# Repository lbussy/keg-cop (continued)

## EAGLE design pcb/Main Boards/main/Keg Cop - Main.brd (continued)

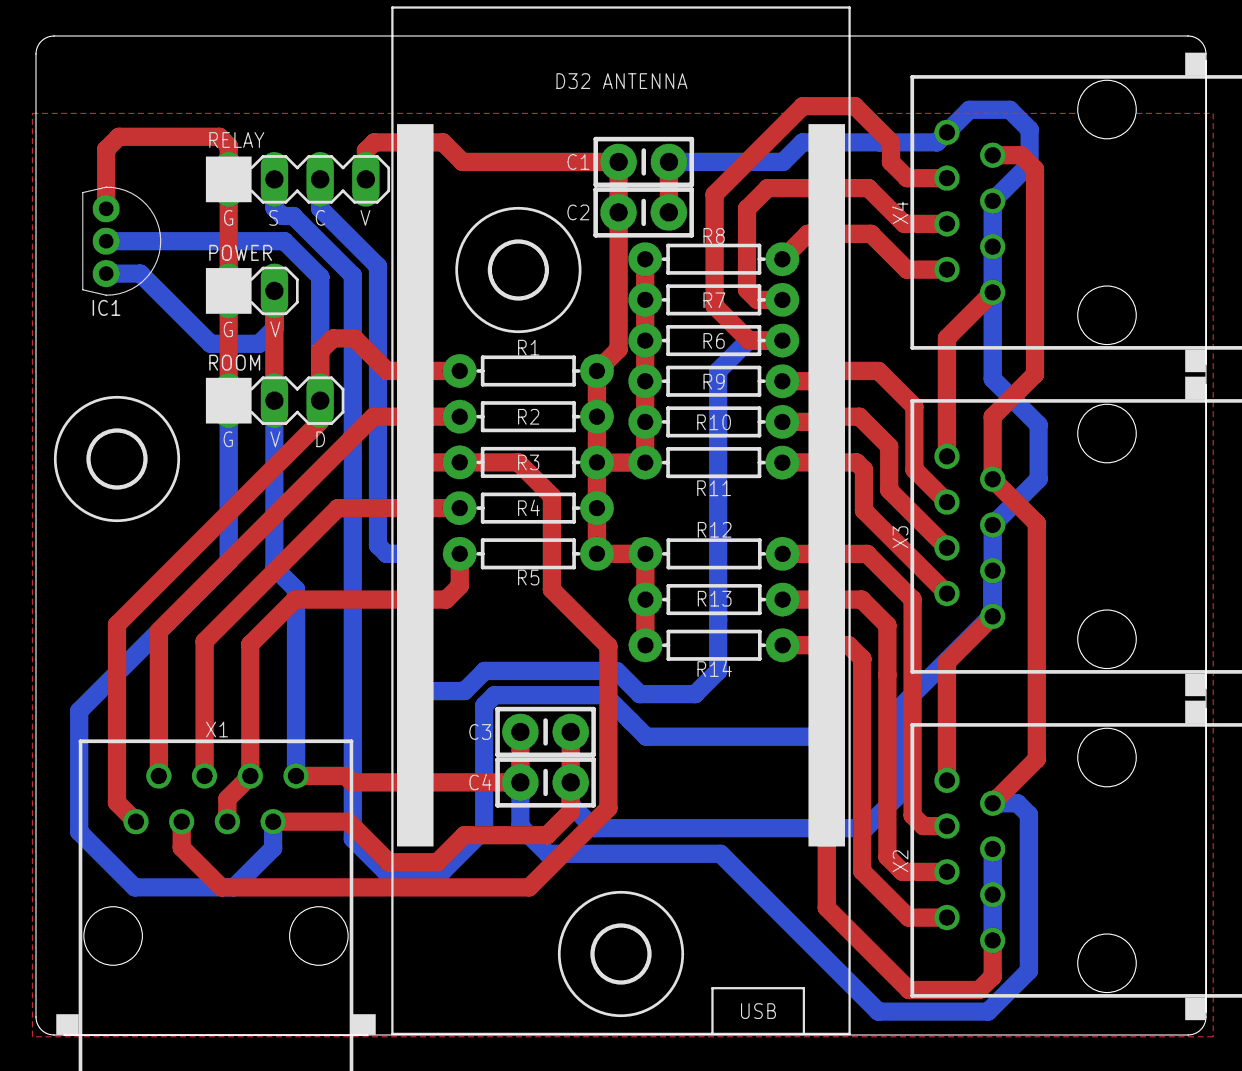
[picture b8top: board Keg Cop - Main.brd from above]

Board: 2 copper layers, 65.0 x 55.5 mm, 30 parts (0 on the bottom side), 19 nets.

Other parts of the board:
U$1, U$2, U$3: 3,0

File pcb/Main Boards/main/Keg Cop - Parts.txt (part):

Partlist exported from C:/Users/lee/OneDrive/Documents/GitHub/keg-cop/pcb/Main Boards/main/Keg Cop - Main.sch at 3/30/2021 6:56 PM

Part  Value     Device               Package        Description                                                                                 ARROW_PART_NUMBER ARROW_PRICE-STOCK DESCRIPTION                           HEIGHT MANUFACTURER_NAME MANUFACTURER_PART_NUMBER MF MOUSER_PART_NUMBER MOUSER_PRICE-STOCK                                                                                     MPN     OC_FARNELL OC_NEWARK POPULARITY PROD_ID VALUE
C1    0.1μF     CAP_CERAMIC_2.54     CAP_PTH-2.54                                                                                                                                                                                                                                                                                                                                                                                                             
C2    1.0μF     CAP_CERAMIC_2.54     CAP_PTH-2.54                                                                                                                                                                                                                                                                                                                                                                                                             
C3    0.1μF     CAP_CERAMIC_2.54     CAP_PTH-2.54                                                                                                                                                                                                                                                                                                                                                                                                             
C4    1.0μF     CAP_CERAMIC_2.54     CAP_PTH-2.54                                                                                                                                                                                                                                                                                                                                                                                                             
D32   Lolin D32 WEMOS-D32D32_NO_BATT D32_NO_BATT    D32_REVERSE is a Reverse silkscreen for placing the Wemos D32 on the underside of the board                                                                                                                                                                                                                                                                                                               
IC1   DS18B20+  DS18B20+             TO-92          DS18B20 prog thermometer 1-Wire, TO92                                                       DS18B20+                            DS18B20 prog thermometer 1-Wire, TO92 mm     Maxim Integrated  DS18B20+                    700-DS18B20+       https://www.mouser.co.uk/ProductDetail/Maxim-Integrated/DS18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                                                      
POWER 2-PIN     HDR-2                HDR-2_VERT                                                                                                                                                                                                                                                                                                                                                                                                               
R1    2.2kΩ     RESISTORAXIAL-0.3    AXIAL-0.3      Generic Resistor Package                                                                                                                                                                                                                                                                                                                                                                                  
R2    2.2kΩ     RESISTORAXIAL-0.3    AXIAL-0.3      Generic Resistor Package                                                                                                                                                                                                                                                                                                                                                                                  
R3    2.2kΩ     RESISTORAXIAL-0.3    AXIAL-0.3      Generic Resistor Package                                                                                                                                                                                                                                                                                                                                                                                  
R4    2.2kΩ     RESISTORAXIAL-0.3    AXIAL-0.3      Generic Resistor Package                                                                                                                                                                                                                                                                                                                                                                                  
R5    2.2kΩ     RESISTORAXIAL-0.3    AXIAL-0.3      Generic Resistor Package                                                                                                                                                                                                                                                                                                                                                                                  
R6    2.2kΩ     RESISTORAXIAL-0.3    AXIAL-0.3      Generic Resistor Package                                                                                                                                                                                                                                                                                                                                                                                  
R7    2.2kΩ     RESISTORAXIAL-0.3    AXIAL-0.3      Generic Resistor Package                                                                                                                                                                                                                                                                                                                                                                                  
R8    2.2kΩ     RESISTORAXIAL-0.3    AXIAL-0.3      Generic Resistor Package                                                                                                                                                                                                                                                                                                                                                                                  
R9    2.2kΩ     RESISTORAXIAL-0.3    AXIAL-0.3      Generic Resistor Package                                                                                                                                                                                                                                                                                                                                                                                  
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
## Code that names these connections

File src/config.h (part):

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// Input pin for keg 0 flow
//
#ifndef FLOW0
#define FLOW0 4
#endif
//
//////////////////////////////////////////////////////////////////////////
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// Input pin for keg 1 flow
//
#ifndef FLOW1
#define FLOW1 16
#endif
//
//////////////////////////////////////////////////////////////////////////
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// Input pin for keg 2 flow
//
#ifndef FLOW2
#define FLOW2 17
#endif
//
//////////////////////////////////////////////////////////////////////////
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// Input pin for keg 3 flow
//
#ifndef FLOW3
#define FLOW3 18
#endif
//
//////////////////////////////////////////////////////////////////////////
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// Input pin for keg 4 flow
//
#ifndef FLOW4
#define FLOW4 19
#endif
//
//////////////////////////////////////////////////////////////////////////
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// Input pin for keg 5 flow
//
#ifndef FLOW5
#define FLOW5 21
#endif
//
//////////////////////////////////////////////////////////////////////////
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// Input pin for keg 6 flow
//
#ifndef FLOW6
#define FLOW6 22
#endif
//
//////////////////////////////////////////////////////////////////////////
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// Input pin for keg 7 flow
//
#ifndef FLOW7
#define FLOW7 23
#endif
//
//////////////////////////////////////////////////////////////////////////
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// Input pin for keg 8 flow
//
#ifndef FLOW8
#define FLOW8 13
#endif
//
//////////////////////////////////////////////////////////////////////////
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
//////////////////////////////////////////////////////////////////////////
//
// Define cool actuator pin
//
#ifndef COOL
#define COOL 27
#endif
//
//////////////////////////////////////////////////////////////////////////
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
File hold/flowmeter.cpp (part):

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const char *kegfilename = "/kegs.json";
extern const size_t capacityKegDeserial = JSON_ARRAY_SIZE(8) + JSON_OBJECT_SIZE(1) + 8*JSON_OBJECT_SIZE(8) + 770;
extern const size_t capacityKegSerial = JSON_ARRAY_SIZE(8) + JSON_OBJECT_SIZE(1) + 8*JSON_OBJECT_SIZE(8);
int kegPins[8] = {KEG0, KEG1, KEG2, KEG3, KEG4, KEG5, KEG6, KEG7};
Flowmeter flow;

static IRAM_ATTR void HandleIntISR0(void)
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
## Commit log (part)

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2022-09-05 Move JSON to stack
2022-09-05 Cleanup strings
2022-09-06 Move back to dynamic type
2022-09-07 Move common function to common file
2022-09-07 Allow builds outside of a repo
2022-09-07 Refactor API
2022-09-08 Add semaphores to prevent windup
2022-09-09 Use SPIFFS Editor
2022-09-09 Finish vestigial file management
2022-09-09 Fix API docs
2022-09-09 Fix API docs (#132)
2022-09-09 Move secret to a header (#133)
2022-09-09 Fix alert bars
2022-09-09 Fix alert bars (#134)
2022-09-09 Enable menu change on sensor change (#135)
2022-09-09 Version bump
2022-09-12 Update KSTV keys
2022-09-12 Remove debug condition on Telnet
2022-09-12 Cleanup debug (#136)
    * Add kstv.json
    * Update KSTV keys
    * Remove debug condition on Telnet
    * Remove debug condition on /edit
2022-09-12 Make keys public, add functions for KS-TV
2022-09-12 Remove needless keys, move KS-TV
2022-09-12 Fix a couple mistakes
2022-09-12 Kstv json (#137)
    * Add kstv.json
    * Update KSTV keys
    * Cleanup debug (#136)
    * Add kstv.json
    * Update KSTV keys
    * Remove debug condition on Telnet
2022-09-12 Don't need string
2022-09-12 Don't need string (#138)
2022-09-18 Move semaphore earlier
2022-09-18 Move reconnect out of callback
2022-09-18 Filesystem stability (#139)
    * Don't need string
    * Change to 5.0 class for SR-only
    * Move semaphore earlier
    * Move reconnect out of callback
    * Clean up filesystem logic
2022-09-18 Filesystem stability (#140)
    * Don't need string
    * Change to 5.0 class for SR-only
    * Move semaphore earlier
    * Move reconnect out of callback
    * Clean up filesystem logic
2022-09-18 Hide page when theme changes (#141)
2022-09-18 Update TODO
2022-09-21 Version update (#142)
2022-09-23 Remove kegscreen service advertisement
2022-09-25 Fix for #146
2023-04-07 Use proper div
2023-04-09 Go back to platform package 1.0.6
2023-04-11 Stub this in for later
2023-04-11 Explicit python decl
2023-04-11 Add .gz handler
2023-04-11 Update uptime refresh
2023-04-12 Ignore data
2023-04-12 I guess I don't need this
2023-04-12 Fix active links
2023-04-12 Fix fan control enabled assignment
2023-04-12 Fix for #152
2023-04-12 Fix for #149
2023-04-13 Version increment
2023-04-14 Restructure reconnect
2023-04-14 Restart serial and telnet
2023-04-14 Restart Web Server
2023-04-14 Reset main loop and filesystem
2023-04-14 Cleanup
2023-04-15 Cleanup logging
2023-04-15 Add some delays to allow Serial to start
2023-04-15 Lockout
2023-04-15 Separate stop and start
2023-04-15 Fix prefixes
2023-04-15 Loop logic
2023-04-15 Set autoconnect off
2023-04-15 Update Bootswatch
2023-04-15 Stub in hourly reboots
2023-04-15 Dis/reconnect on iter
2023-04-16 Reboot every 1 hour to avoid panic
2023-04-16 Logging cleanup
2023-04-16 Change to 2 hour reboot
2023-04-16 Standardize logic
2023-04-16 Tag new alpha
2023-04-18 Close FS after use
2023-04-19 Use single open/close
2023-04-19 Add delay to see startup Serial
2023-04-21 Fix John's 'feature'
2023-04-21 Refactor return
2023-04-22 Move theme to info
2023-04-23 Get rid of some harmless 404 erors
2023-04-23 Reset to 42 day reboot
2023-04-23 Add new file handler
2023-04-23 Fixed asynch error
2023-04-23 Update LCBUrl to HEAD
2023-04-23 Reverse order of debug
2023-04-23 Remove debug
2023-04-23 Change execution order
2023-04-25 Rearranged to allow flow load
2023-04-25 Nail down LCBUrl version
2023-04-29 Replace appconfig keys
2023-04-29 Add realm to authentication
2023-04-29 Stylize file buttons
2023-04-30 Add link to /fs/
2023-04-30 Style other buttons
2023-04-30 Exclude delete/download buttons
2023-04-30 Style/cancel upload
2023-05-11 Additional FS cleanup - stopping point
2023-05-11 Keep track of TODO
2023-05-11 Add debug
2023-05-11 Fix concatenation
2023-05-11 Add default TIO labels
2023-05-11 Fix label default
2023-05-11 Limit debug printing when file is missing
2023-05-11 Replace missing file
2023-05-11 Update version tag
2023-05-11 Realm is busted
2023-05-11 Restyle file list
2023-05-11 Disable/enable buttons
2023-05-11 Timeout messages
2023-05-11 Disable uploads
2023-05-13 Test uploads
2023-05-13 Rearrange events
2023-05-13 Pretty code
2023-05-13 Remive unused function
2023-05-13 Add secret to fs actions
2023-05-13 Add filename to prompt
2023-05-14 Restore file upload (#182)
    * Test uploads
    * Remove comments
    * Rearrange events
    * Pretty code
    * Remive unused function
    * Create new file upload
2023-05-14 Document fs page
2023-05-14 Remove /files/ from info
2023-05-14 Self-document fs API
2023-05-15 Split functions
2023-05-15 Document split fs api
2023-05-15 Fix file status display
2023-05-15 Update image
2023-05-15 Add fs api documentation
2023-05-15 Document fs (#183)
    * Document fs page
    * Self-document fs API
    * Fix file status display
    * Update image
    * Add fs api documentation
2023-05-15 Queue saves
2023-05-16 No longer used
2023-05-16 Use updated ArduinoJson
2023-05-16 Remove stupid workaround
2023-05-16 Add a better 404 handler
2023-05-16 Move to LittleFS
2023-05-16 Move license to md
2023-05-19 Littlefs (#186)
    * Move to LittleFS
    * Move license to md
2023-05-19 Avoid non reentrant code (#187)
2023-05-20 Fix viewport (#188)
2023-05-20 Rearrange fatal error
2023-05-20 Reset log priorities
2023-05-21 Add failure detect to app load
2023-05-21 Add debug to models
2023-05-21 Add handler for debug settings
2023-05-21 Add loglevel to serial init
2023-05-23 Add copy file function
2023-05-23 Leave notes
2023-05-23 Get rid of unneeded TODOs
2023-05-23 Use arguments for JSON load/save functions
2023-05-26 Update comments
2023-05-26 Leave myself a note
2023-05-29 Fix return
2023-05-29 Attempt config reload
2023-05-29 Backup config (#190)
    * Add failure detect to app load
    * Add copy file function
    * Handle LittleFS or SPIFFS
    * Use arguments for JSON load/save functions
    * Create backup after good file save
    * Fix return
2023-05-29 Backup config (#190)
    * Add failure detect to app load
    * Add copy file function
    * Handle LittleFS or SPIFFS
    * Use arguments for JSON load/save functions
    * Create backup after good file save
    * Fix return
2023-05-31 Update telnet lib
2023-05-31 Add telnet to web handler
2023-05-31 Add loglevel to web handler
2023-06-01 Add telnet and loglevel info
2023-06-01 Fix some scaling
2023-06-01 Change URL Target to Generic Rest
2023-06-01 Change URL Target to Generic Rest (#191)
2023-06-06 Bump version to Beta
2023-06-06 Fix docs requirements
2023-06-07 Handle LittleFS
2023-06-07 Add defaults
2023-06-07 Add back in async settings
2023-06-07 Restore saving theme
2023-06-07 Wrap debug settings in form
2023-06-07 Fix settings debug (#193)
    * Handle LittleFS
    * Fix debug line
    * Add defaults
    * Add back in async defines
    * Fix debug load
    * Restore saving theme
2023-06-08 Use explicit paths
2023-06-08 Reorder page handlers
2023-06-08 Fix routes
2023-06-08 Fs errors (#194)
    * Use explicit paths
    * Compress PNG too
    * Reorder page handlers
    * Fix routes
2023-06-08 Revert "Fs errors (#194)"
    This reverts commit 4d5f7bd300830cc77d4469af5861f50ff3dcb13e.
2023-06-08 Fs errors (#196)
    * Use explicit paths
    * Compress PNG too
    * Reorder page handlers
    * Fix routes
    * Turn off core debug
2023-06-08 Revert route changes
2023-06-08 Stub out nerw files
2023-06-08 New functions
2023-06-08 Start moving towards sync MQTT
2023-06-09 Remove RPints from setup
2023-06-09 Remove unused code
2023-06-09 Set up to use generic push
2023-06-09 No longer needed
2023-06-09 Move defines out of indiv headers
2023-06-09 Move wifihandler defines out of headers
2023-06-09 Move version defines out of headers
2023-06-09 Move urltarget defines out of headers
2023-06-09 Move uptimelog defines out of headers
2023-06-09 Move tools defines out of headers
2023-06-09 Move thermostat defines out of headers
2023-06-09 Move tempsensor defines out of headers
2023-06-09 Move taplistio defines out of headers
2023-06-09 Move resetreasons defines out of headers
2023-06-09 Move ntphandler defines out of headers
2023-06-09 Move main defines out of headers
2023-06-09 Move kegscreen defines out of headers
2023-06-09 Move flowconfig defines out of headers
2023-06-09 Move execota defines out of headers
2023-06-09 Move appconfig defines out of headers
2023-06-09 Protect Includes & Defines (#197)
    * Move defines out of indiv headers
    * Move wifihandler includes out of headers
    * Move webpagehandler includes out of headers
    * Move version includes out of headers
    * Move urltarget includes out of headers
    * Move uptimelog includes out of headers
2023-06-10 New RPints push
2023-06-10 Get rid of old notes
2023-06-10 Address templating and push logic
2023-06-10 Fix RPints template
2023-06-10 Fix pulse reports
2023-06-10 RPints push finished
2023-06-10 Switch MQTT Libs (#198)
    * Go back to a normal MQTT lib
    * Remove RPints from setup
    * Set up to use generic push
    * Protect Includes & Defines (#197)
    * New RPints push
    * Address templating and push logic
2023-06-11 Clean up logging
2023-06-11 Add HA config to settings
2023-06-11 Add Mosquitto setup steps to troubleshooting
2023-06-11 Update documentation for HA context
2023-06-11 Handle HA config post
2023-06-11 Add HA files
2023-06-12 Rough out functions
2023-06-16 Change field to password
2023-06-16 Initial device discovery
2023-06-16 Normalize abbrev
2023-06-20 Working templates
2023-06-21 Change log level
2023-06-21 Re-use portions of template
2023-06-21 Fix status for binaries
2023-06-21 Send only when enabled
2023-06-23 Initial HASS push on startup
2023-06-24 Remove spam
2023-06-24 Add in state changes
2023-06-25 Change default logging
2023-06-25 Queue HASS functions
2023-06-25 Queuing and availability
2023-06-25 GEt rid of vestigal JSON code
2023-06-25 Update MQTT documentation
2023-06-25 Use initial and ongoing timer for HASS
2023-06-25 Get rid of compiler warning
2023-06-25 Reduce logging level
2023-06-26 Add single point re-broadcast
2023-06-26 Fix solenoid state
2023-06-26 Fixed logic
2023-06-26 MQTT update for only selected sensor
2023-06-26 MQTT update for unavailable too
2023-06-26 Make change on tap post
2023-06-26 Reset control state on sensor unavail
2023-06-30 Disable CP when sensor is disabled
2023-06-30 Home asst (#199)
    * Switch MQTT Libs (#198)
    * Set up to use generic push
    * Protect Includes & Defines (#197)
    * New RPints push
    * Address templating and push logic
    * Get rid of 24hr timer
2023-07-08 Add kickdetect to web settings
2023-07-08 Add kickdetect to settings
2023-07-08 Allow skipping kickdetect
2023-07-08 Change verbiage
2023-07-08 Config kick detect (#200)
    * Update TODO
    * Add kickdetect to model
    * Add kickdetect to web settings
    * Add kickdetect to settings
    * Add kickdetect to API
    * Allow skipping kickdetect
2023-07-16 Allow a reconect
2023-07-16 Fix temp page control link
2023-07-19 Bunp version
2023-07-19 Feature Release 1.3.0 (#202)
    * Remove kegscreen service advertisement
    * Fix mDNS keys
    * Fix for #146
    * Use proper div
    * Add scanNetworks() to reconnect
    * Go back to platform package 1.0.6
2023-07-28 Document Home Assistant integration (#203)
2023-08-16 Update readthedocs.yaml
    The `build.image` config key on `.readthedocs.yaml` has been deprecated, and will be removed on October 16, 2023.
2023-08-16 Rename images
2023-08-16 Devel doc (#204)
    * Document Home Assistant integration (#203)
    * Update readthedocs.yaml
    The `build.image` config key on `.readthedocs.yaml` has been deprecated, and will be removed on October 16, 2023.
    * Rename images
    * Run through grammarly
    ---------
2023-08-16 Devel doc (#205)
    * Document Home Assistant integration (#203)
    * Update readthedocs.yaml
    The `build.image` config key on `.readthedocs.yaml` has been deprecated, and will be removed on October 16, 2023.
    * Rename images
    * Run through grammarly
    * Need py <= 3.8
2023-08-16 Still hammering on readthedocs
2023-08-16 Devel doc (#207)
    * Document Home Assistant integration (#203)
    * Update readthedocs.yaml
    The `build.image` config key on `.readthedocs.yaml` has been deprecated, and will be removed on October 16, 2023.
    * Rename images
    * Run through grammarly
    * Need py <= 3.8
2023-08-16 Integrate HASS Customization
2023-08-16 Devel doc (#208)
    * Document Home Assistant integration (#203)
    * Update readthedocs.yaml
    The `build.image` config key on `.readthedocs.yaml` has been deprecated, and will be removed on October 16, 2023.
    * Rename images
    * Run through Grammarly
    * Need py == 3.10
